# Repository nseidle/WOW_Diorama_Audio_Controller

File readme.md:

WOW Story Time Tree
==============

The story time tree exhibit allows children to view a diorama through a small window. Pressing a button plays sounds of nature, a story teller, or other tracks related to the scene. When a button is pressed the scene is illuminated. The handset is a modified telephone and phone hook to increase reliability and reduce cost. The knob controls volume. Each button plays a series of tracks, looping if the user continues to press the button.

The system monitors the state of 5 buttons. When a button is pressed a string of LEDs is lit and plays the corresponding MP3 track. I designed a custom shield to allow for JST connections to each channel (LED+button). 

Materials used:

* [SparkFun RedBoard Plus](https://www.sparkfun.com/sparkfun-redboard-plus.html)
* A whole bunch of [Arcade Buttons](https://www.sparkfun.com/products/9336)
* [SparkFun MP3 Shield](https://www.sparkfun.com/products/12660)
* [MicroSD Card](https://www.sparkfun.com/products/11609) (Any size up to 64GB behemoths should do)
* [10k Trimpot for volume](https://www.sparkfun.com/products/9806)
* [Metal volume knob](https://www.sparkfun.com/silver-metal-knob-14x24mm.html)
* Custom Arduino R3 shield (this repo, see hardware folder) to interface to five buttons and one LED strip
* [5x 3-pin JST cable](https://www.sparkfun.com/jst-to-breadboard-jumper-3-pin.html) connections to the illuminated buttons
* [2-pin JST cable](https://www.sparkfun.com/jst-jumper-2-wire-assembly.html) connection to the LED illumination of the scene

3D Printed Parts
-------------------
The phone handset is cut and modified with a [3D printed part](https://github.com/nseidle/WOW_Diorama_Audio_Controller/blob/main/Models/WOWPhoneAttachment.stl).

License Information
-------------------
The **code** is drinkware; if you see me (or any other SparkFun employee) at the local, and you've found our code helpful, please buy us a round!

Please use, reuse, and modify these files as you see fit. Please maintain attribution to SparkFun Electronics and release anything derivative under the same license.

Distributed as-is; no warranty is given.

- Your friends at SparkFun.

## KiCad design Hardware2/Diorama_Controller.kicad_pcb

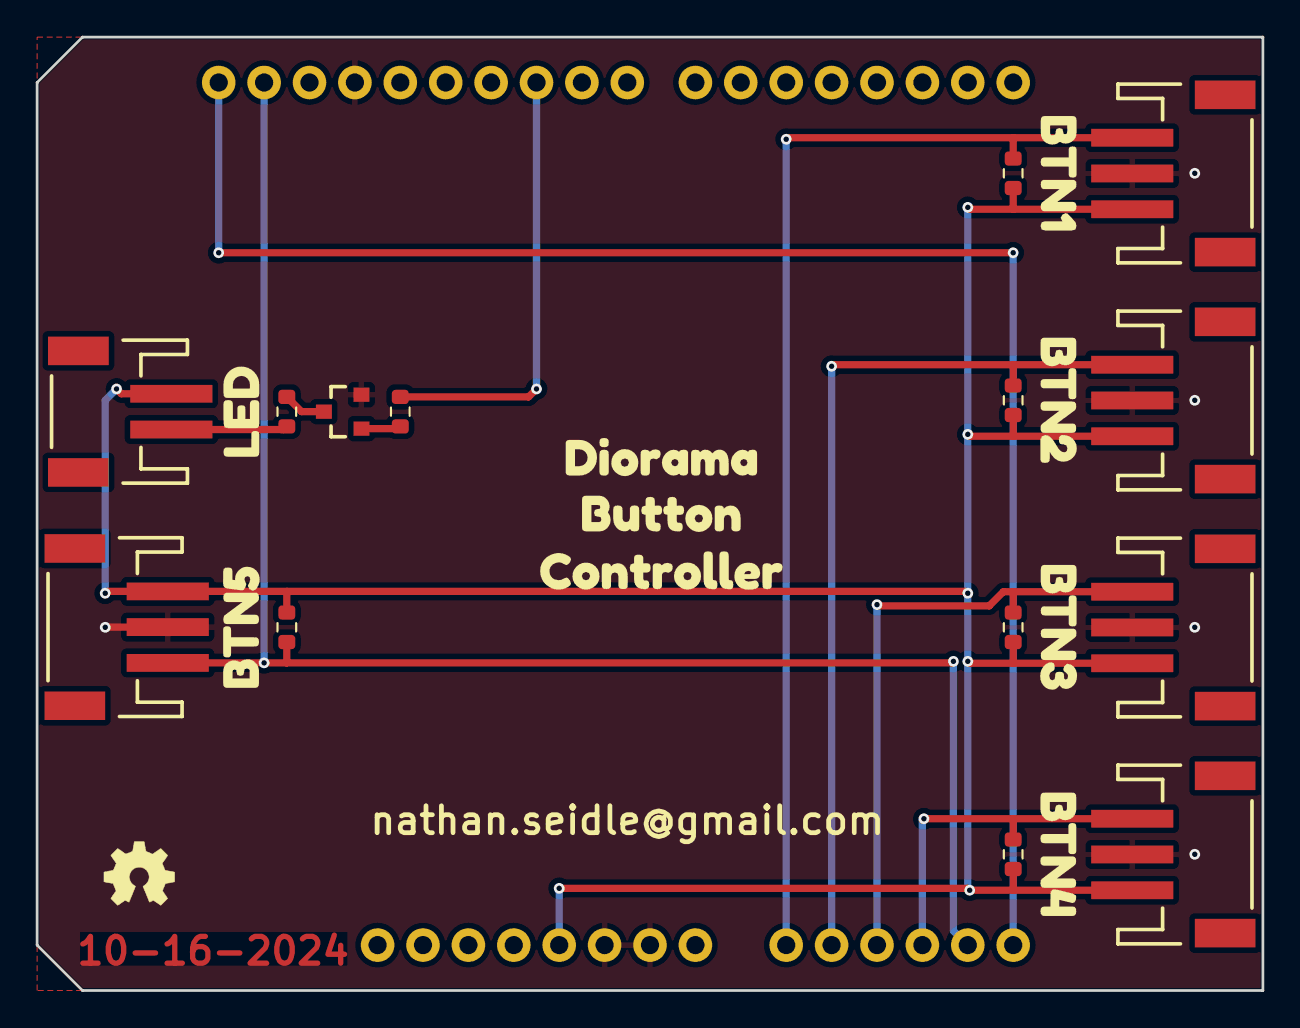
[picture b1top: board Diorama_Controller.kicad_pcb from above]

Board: 2 copper layers, 68.6 x 53.3 mm, 26 parts (0 on the bottom side), 11 nets.

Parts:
B1: Arduino_Uno_R3_Shield; Uno_R3_Shield_NoLabels
G1: OSHW_Logo; Creative_Commons_License
J1, J2, J3, J4, J6: JST_2mm_3; JST_SMD_2.0mm-3
J5: JST_2mm_LiPo; JST_SMD_2.0mm-2
Q1: MMBT2222A; SOT23-3
R1, R2, R3, R4, R5: 10k; R_0603_1608Metric
R7: 330; R_0603_1608Metric
R8: 33; R_0603_1608Metric
Ref**: Val**; OSHW_Logo_4mm
kibuzzard-671AF94E: G***; kibuzzard-671AF94E
kibuzzard-671AF894: G***; kibuzzard-671AF894
kibuzzard-671AF941: G***; kibuzzard-671AF941
kibuzzard-671AF949: G***; kibuzzard-671AF949
kibuzzard-6713271F: G***; kibuzzard-6713271F
kibuzzard-6713273F: G***; kibuzzard-6713273F
kibuzzard-67132771: G***; kibuzzard-67132771
kibuzzard-67132779: G***; kibuzzard-67132779
kibuzzard-67132780: G***; kibuzzard-67132780

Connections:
5V: B1.5V, J1.3, J2.3, J3.3, J4.3, J5.2 (+), J6.3, R1.2, R2.2, R3.2, R4.2, R5.2
BTN1: B1.A0, J2.1, R1.1
BTN2: B1.A1, J1.1, R2.1
BTN3: B1.A2, J3.1, R3.1
BTN4: B1.A3, J4.1, R4.1
BTN5: B1.A4/SDA, J6.1, R5.1
GND: B1.GND, J1.2, J2.2, J3.2, J4.2, J6.2, Q1.2 (E)
LED0: B1.D10 (*D10), R7.2
unnamed: J5.1 (-), R8.2
unnamed: Q1.1 (B), R7.1
unnamed: Q1.3 (C), R8.1

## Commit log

2025-02-16 Update readme. Add image. Update ignore.
2025-02-20 Add 3D files
2025-02-20 Add internal photos

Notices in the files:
parts and their libraries:
https://creativecommons.org/licenses/by-sa/4.0
Released under the Creative Commons Attribution Share-Alike 4.0 License
